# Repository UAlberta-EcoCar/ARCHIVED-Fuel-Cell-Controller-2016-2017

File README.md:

# Fuel-Cell-Controller
Custom controller for a 28 cell Ballard Fuel Cell

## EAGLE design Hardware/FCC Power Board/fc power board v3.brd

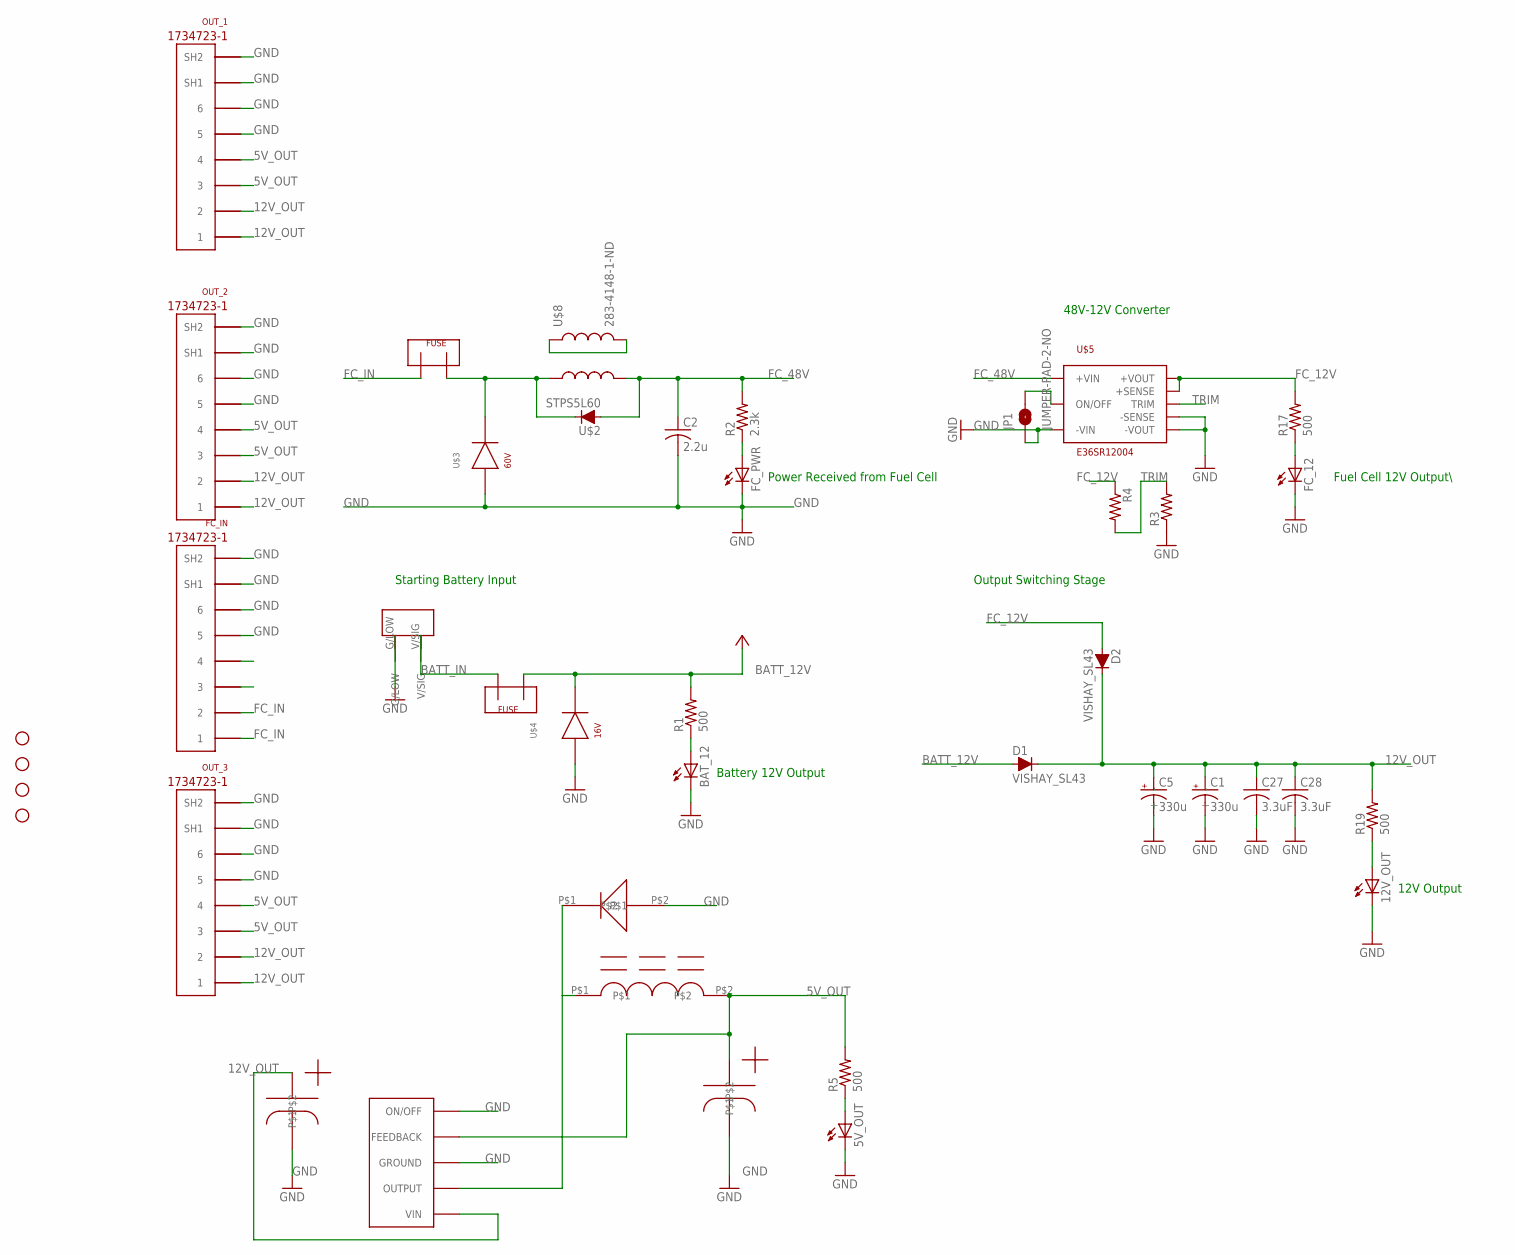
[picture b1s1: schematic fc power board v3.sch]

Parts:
5V_OUT, 12V_OUT: LED1206; LED-1206
BATTERY_FUSE: FUSEMINI-BLADE; MINI-BLADE-FUSE
BAT_12: LED1206; LED-1206
C1, C5: 330u; 399-6608-ND
C2: 2.2u; C0805
C27, C28: 3.3uF; C0805
D1, D2: VISHAY_SL43; DO-214AB_SMC
FC_12: LED1206; LED-1206
FC_IN: 5555140-6; 1734723-1_RJ11
FC_PWR: LED1206; LED-1206
JP1: JUMPER-PAD-2-NO; PAD-JUMPER-2-NO_NO_SILK
OUT_1, OUT_2, OUT_3: 5555140-6; 1734723-1_RJ11
R1, R5, R17: 500; R0805
R2: 2.3k; R0805
R3, R4: R-US_R0805; R0805
R19: 500; M0805
STANDOFF1, STANDOFF2, STANDOFF3, STANDOFF4: STAND-OFF
U$1: MBR360GOS
U$2: STPS5L60; STM_SMC
U$3: SMBJ60CA; .277X.089
U$4: SMAJ16CA; .25X.07
U$5: E36SR12004; 2.30X0.90X0.34
U$7: FUSEMINI-BLADE; MINI-BLADE-FUSE
U$8: 283-4148-1-ND
U$9: 2_PIN_TECONNECTOR; 2_PIN_CONNECT
U$13: LM2576; D2PAK-5
U$14: CAPESK107M025AC3AA; ESK107M025AC3AA
U$15: CAPESK108M025AH4EA; ESK108M025AH4EA
U$16: M1418-ND

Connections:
5V_OUT: OUT_1.3, OUT_1.4, OUT_2.3, OUT_2.4, OUT_3.3, OUT_3.4, R5.2, U$13.4 (FEEDBACK), U$15.P$1, U$16.P$2
12V_OUT: C1.PLUS (+), C5.PLUS (+), C27.1, C28.1, D1.C, D2.C, OUT_1.1, OUT_1.2, OUT_2.1, OUT_2.2, OUT_3.1, OUT_3.2, R19.2, U$13.1 (VIN), U$14.P$1
BATT_12V: BATTERY_FUSE.OUT, D1.A, R1.2, U$4.CATHODE
BATT_IN: BATTERY_FUSE.IN, U$9.V/SIG
FC_12V: D2.A, R4.1, R17.2, U$5.P$7 (+SENSE), U$5.P$8 (+VOUT)
FC_48V: C2.1, R2.2, U$2.A, U$5.P$1 (+VIN), U$8.P$3 (2)
FC_FUSED: U$2.C, U$3.CATHODE, U$7.IN, U$8.P$1 (1)
FC_IN: FC_IN.1, FC_IN.2, U$7.OUT
GND: 5V_OUT.C, 12V_OUT.C, BAT_12.C, C1.MINUS (-), C2.2, C5.MINUS (-), C27.2, C28.2, FC_12.C, FC_IN.5, FC_IN.6, FC_IN.SH1, FC_IN.SH2, FC_PWR.C, JP1.1, OUT_1.5, OUT_1.6, OUT_1.SH1, OUT_1.SH2, OUT_2.5, OUT_2.6, OUT_2.SH1, OUT_2.SH2, OUT_3.5, OUT_3.6, OUT_3.SH1, OUT_3.SH2, R3.1, U$1.P$2, U$3.ANODE, U$4.ANODE, U$5.P$3 (-VIN), U$5.P$4 (-VOUT), U$5.P$5 (-SENSE), U$9.G/LOW, U$13.3 (GROUND), U$13.5 (ON/OFF), U$13.GROUND, U$14.P$2, U$15.P$2
unnamed: JP1.2, U$5.P$2 (ON/OFF)
unnamed: BAT_12.A, R1.1
unnamed: FC_PWR.A, R2.1
unnamed: U$8.P$2 (3), U$8.P$4 (4)
unnamed: 5V_OUT.A, R5.1
unnamed: U$1.P$1, U$13.2 (OUTPUT), U$16.P$1
unnamed: FC_12.A, R17.1
unnamed: 12V_OUT.A, R19.1
TRIM: R3.2, R4.2, U$5.P$6 (TRIM)

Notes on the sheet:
Output Switching Stage
Starting Battery Input
48V-12V Converter
Power Received from Fuel Cell
Battery 12V Output
Fuel Cell 12V Output\
12V Output

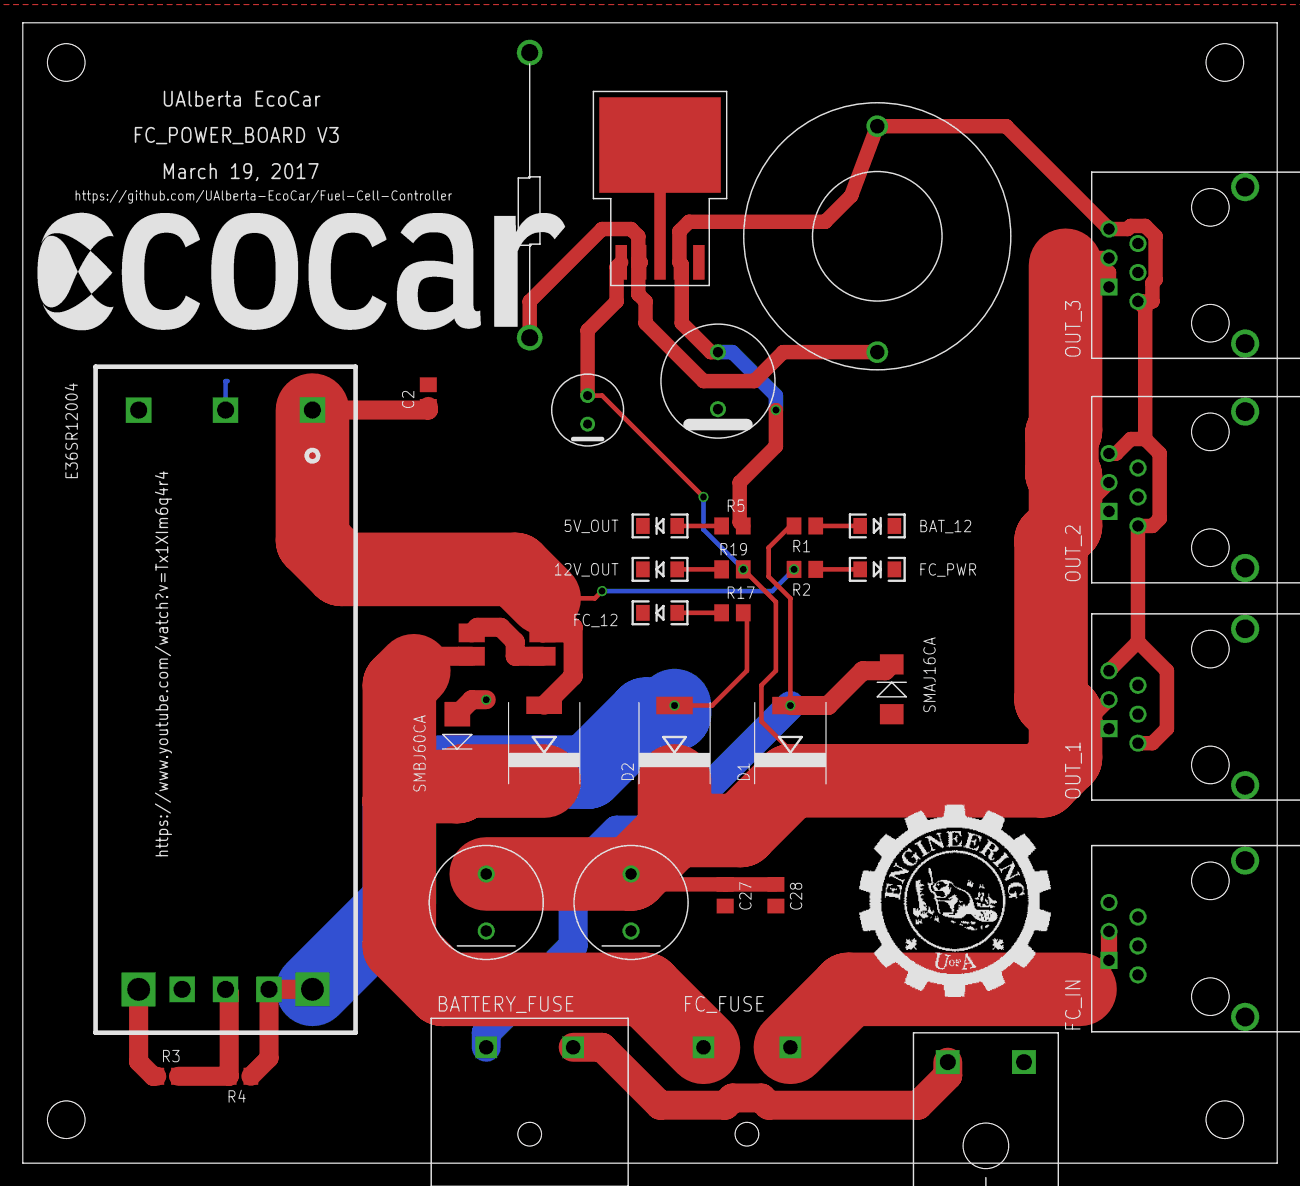
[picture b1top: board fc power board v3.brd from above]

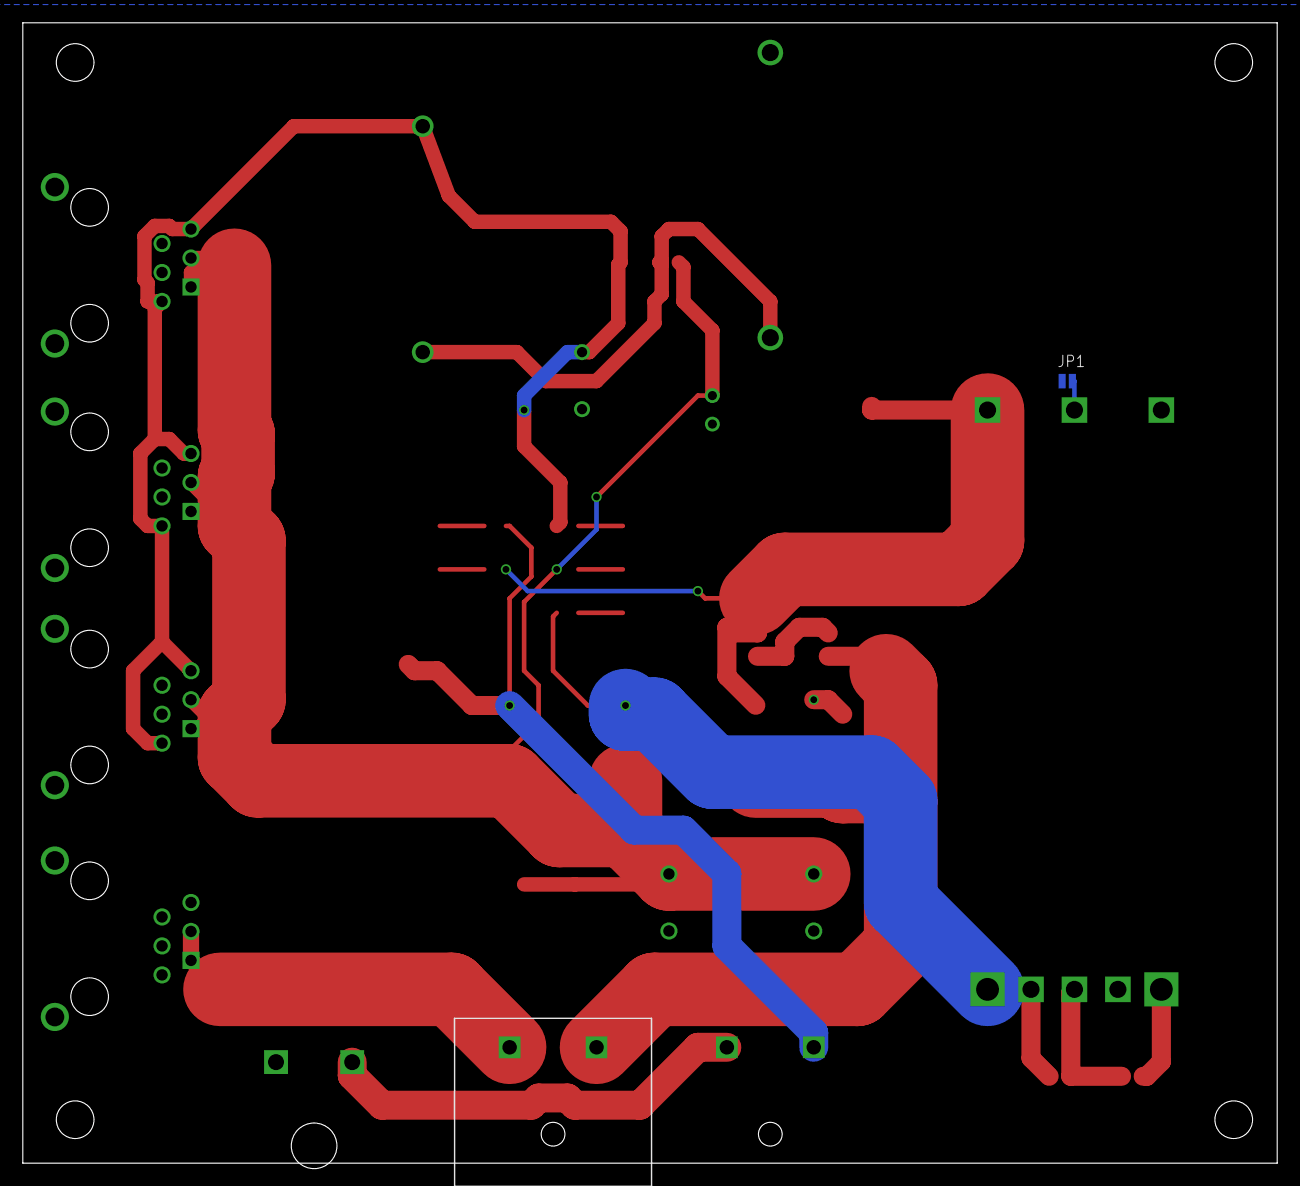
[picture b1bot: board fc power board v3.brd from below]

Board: 2 copper layers, 110.0 x 100.0 mm, 42 parts (2 on the bottom side), 18 nets.

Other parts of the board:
U$6: ECOCAR_LOGO_2018

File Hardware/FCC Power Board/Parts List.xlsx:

Capacitors
399-6608-ND |  | 2
ESK108M025AH4EA |  | 1
ESK107M025AC3AA |  | 1
3.3 uF |  | 2
Inductors
M1418-ND |  | 1
283-4148-1-ND |  | 1
Fuse Holder
F064-ND |  | 2
TVS Diode
SMAJ16CA |  | 1
SMBJ60CA |  | 1
Blocking Diodes
STPS5L60 |  | 3
MBR360GOS |  | 1
Block Power Converter
E36SR12004 |  | 1
12 to 5 regulator
LM2576D2TR4-5GOSCT-ND |  | 1
Resistors
500 |  | 3
2300 |  | 1

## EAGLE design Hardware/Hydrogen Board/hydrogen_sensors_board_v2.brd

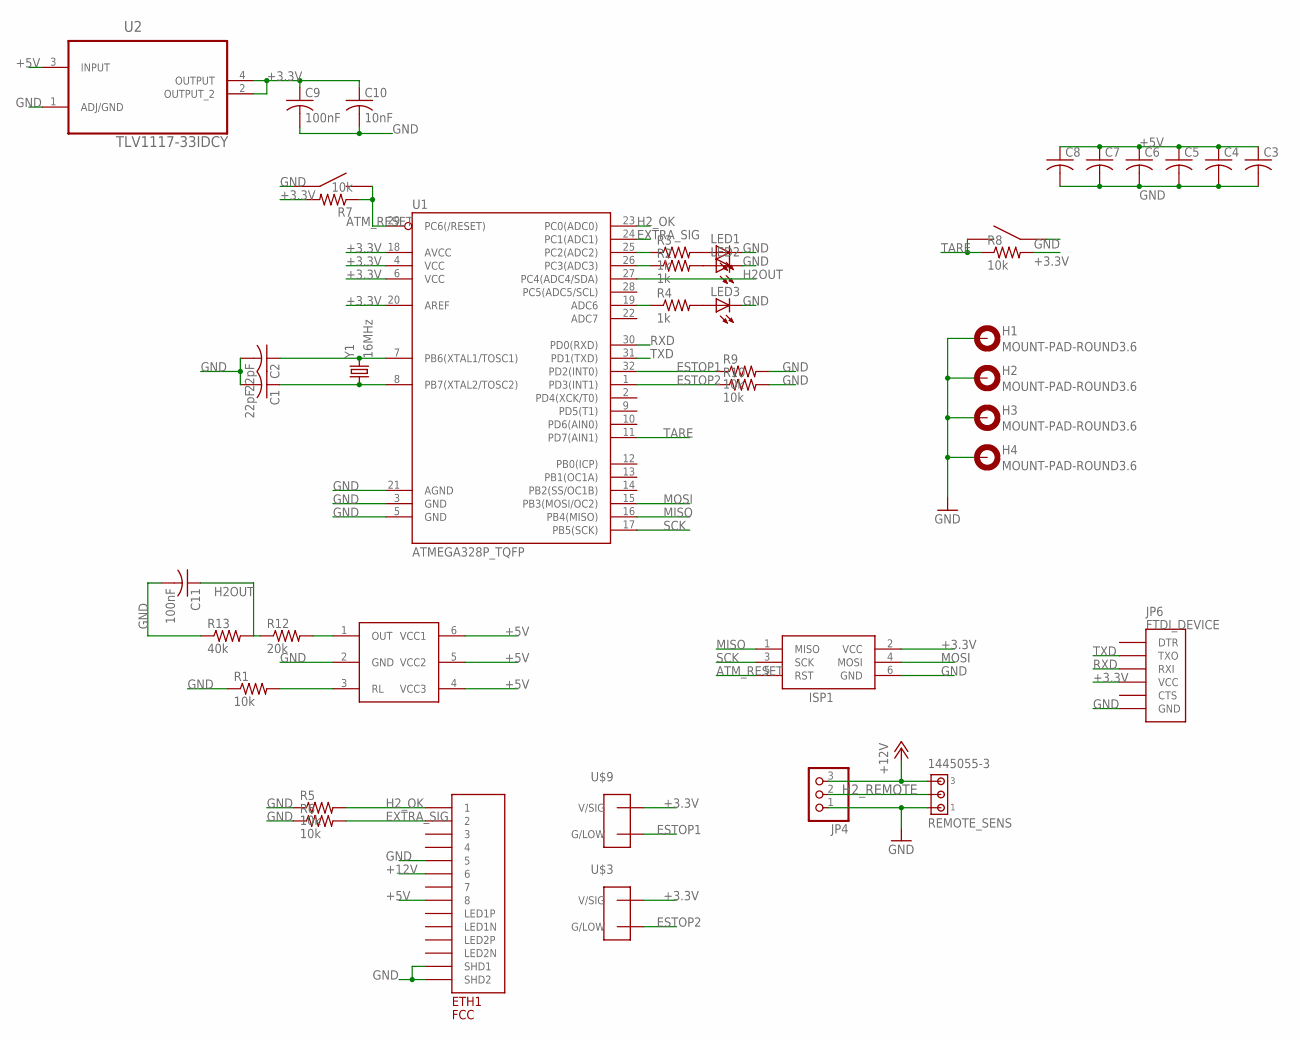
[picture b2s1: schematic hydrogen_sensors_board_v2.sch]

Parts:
C1, C2: 22pF; C0603K
C3, C4, C5, C6, C7, C8: C-USC0603; C0603
C9, C11: 100nF; C0603
C10: 10nF; C0603
ETH1: FCC; A122645-ND
H1, H2, H3, H4: MOUNT-PAD-ROUND3.6; 3,6-PAD
ISP1: AVRISP-BOX
JP4: PINHD-1X3; 1X03
JP6: FTDI_DEVICE; FTDI_DEVICE_SIDE
LED1, LED2, LED3: LEDCHIPLED_0805; CHIPLED_0805
R1, R5, R6, R7, R8, R9, R10: 10k; 0603-RES
R2, R3, R4: 1k; 0603-RES
R12: 20k; 0603-RES
R13: 40k; 0603-RES
REMOTE_SENS: 1445055-3
U1: ATMEGA328P_TQFP; TQFP32-08
U2: TLV1117-33IDCY; SOT230P700X180-4N
U$1: MQ-8MQ-8; MQ-8
U$2, U$10: EG4621CT-ND
U$3, U$9: TE770966; 2X1-MATE-N-LOCK
Y1: 16MHz; HC49US

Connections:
+3.3V: C9.1, C10.1, ISP1.2 (VCC), JP6.P$4 (VCC), R7.2, R8.2, U1.4 (VCC), U1.6 (VCC), U1.18 (AVCC), U1.20 (AREF), U2.2 (OUTPUT_2), U2.4 (OUTPUT), U$3.CIRCUIT1 (V/SIG), U$9.CIRCUIT1 (V/SIG)
+5V: C3.1, C4.1, C5.1, C6.1, C7.1, C8.1, ETH1.P$8 (8), U2.3 (INPUT), U$1.4 (VCC3), U$1.5 (VCC2), U$1.6 (VCC1)
+12V: ETH1.P$6 (6), JP4.3, REMOTE_SENS.3
ATM_RESET: ISP1.5 (RST), R7.1, U1.29 (PC6(/RESET)), U$10.P$3, U$10.P$4
ESTOP1: R9.1, U1.32 (PD2(INT0)), U$9.CIRCUIT2 (G/LOW)
ESTOP2: R10.1, U1.1 (PD3(INT1)), U$3.CIRCUIT2 (G/LOW)
EXTRA_SIG: ETH1.P$2 (2), R6.2, U1.24 (PC1(ADC1))
GND: C1.2, C2.2, C3.2, C4.2, C5.2, C6.2, C7.2, C8.2, C9.2, C10.2, C11.2, ETH1.P$5 (5), ETH1.P$13 (SHD1), ETH1.P$14 (SHD2), H1.B3,6, H2.B3,6, H3.B3,6, H4.B3,6, ISP1.6 (GND), JP4.1, JP6.P$6 (GND), LED1.C, LED2.C, LED3.C, R1.1, R5.1, R6.1, R9.2, R10.2, R13.1, REMOTE_SENS.1, U1.3 (GND), U1.5 (GND), U1.21 (AGND), U2.1 (ADJ/GND), U$1.2 (GND), U$2.P$1, U$2.P$2, U$10.P$1, U$10.P$2
H2OUT: C11.1, R12.1, R13.2, U1.27 (PC4(ADC4/SDA))
H2_OK: ETH1.P$1 (1), R5.2, U1.23 (PC0(ADC0))
H2_REMOTE: JP4.2, REMOTE_SENS.2
MISO: ISP1.1 (MISO), U1.16 (PB4(MISO))
MOSI: ISP1.4 (MOSI), U1.15 (PB3(MOSI/OC2))
unnamed: C2.1, U1.7 (PB6(XTAL1/TOSC1)), Y1.2
unnamed: R1.2, U$1.3 (RL)
unnamed: C1.1, U1.8 (PB7(XTAL2/TOSC2)), Y1.1
unnamed: R3.1, U1.25 (PC2(ADC2))
unnamed: R2.1, U1.26 (PC3(ADC3))
unnamed: R4.1, U1.19 (ADC6)
unnamed: LED1.A, R3.2
unnamed: LED2.A, R2.2
unnamed: LED3.A, R4.2
unnamed: R12.2, U$1.1 (OUT)
RXD: JP6.P$3 (RXI), U1.30 (PD0(RXD))
SCK: ISP1.3 (SCK), U1.17 (PB5(SCK))
TARE: R8.1, U1.11 (PD7(AIN1)), U$2.P$3, U$2.P$4
TXD: JP6.P$2 (TXO), U1.31 (PD1(TXD))

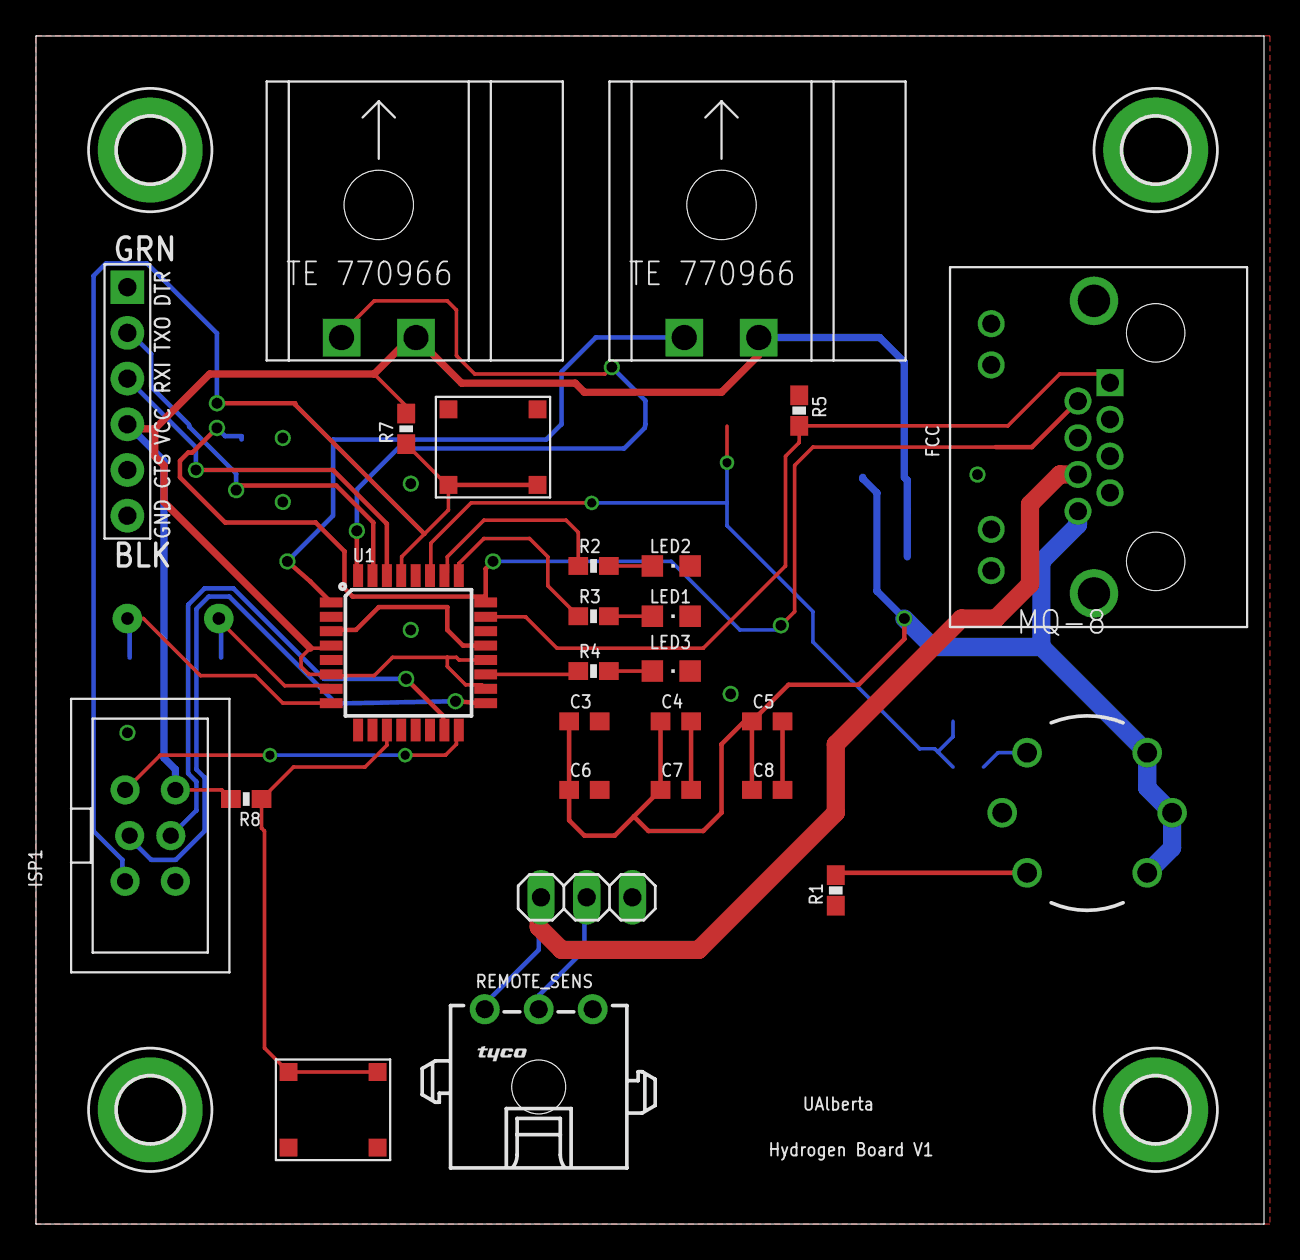
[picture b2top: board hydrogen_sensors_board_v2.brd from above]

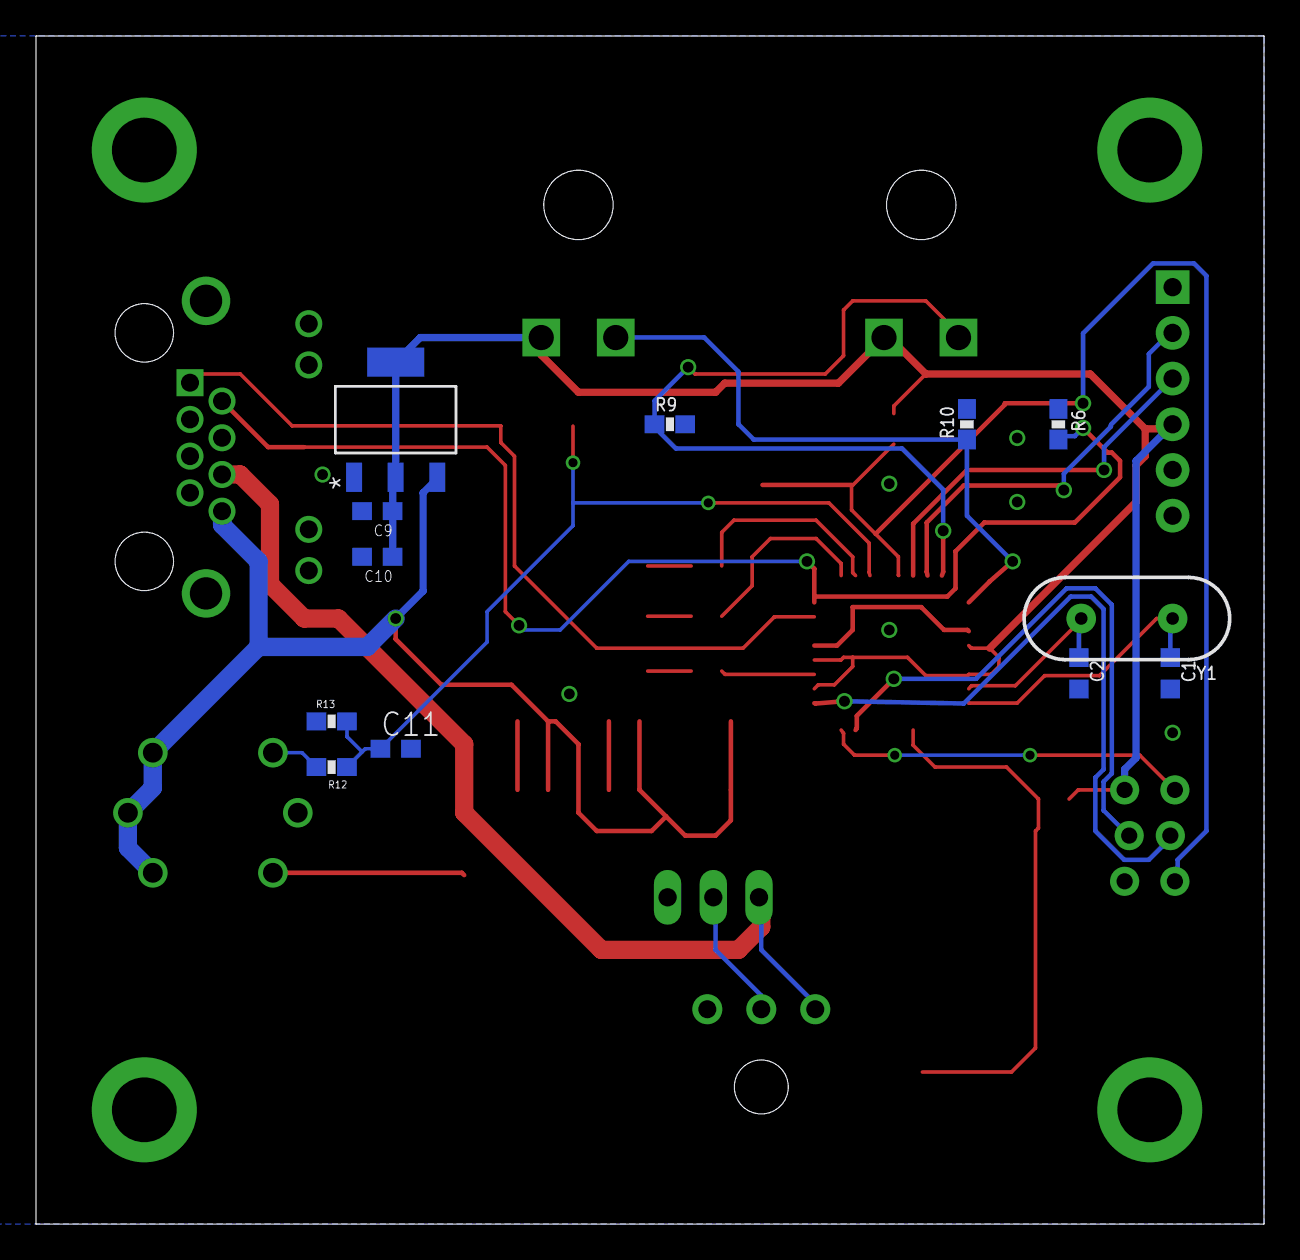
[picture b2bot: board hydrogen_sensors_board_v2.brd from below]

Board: 2 copper layers, 68.2 x 66.0 mm, 43 parts (12 on the bottom side), 27 nets.

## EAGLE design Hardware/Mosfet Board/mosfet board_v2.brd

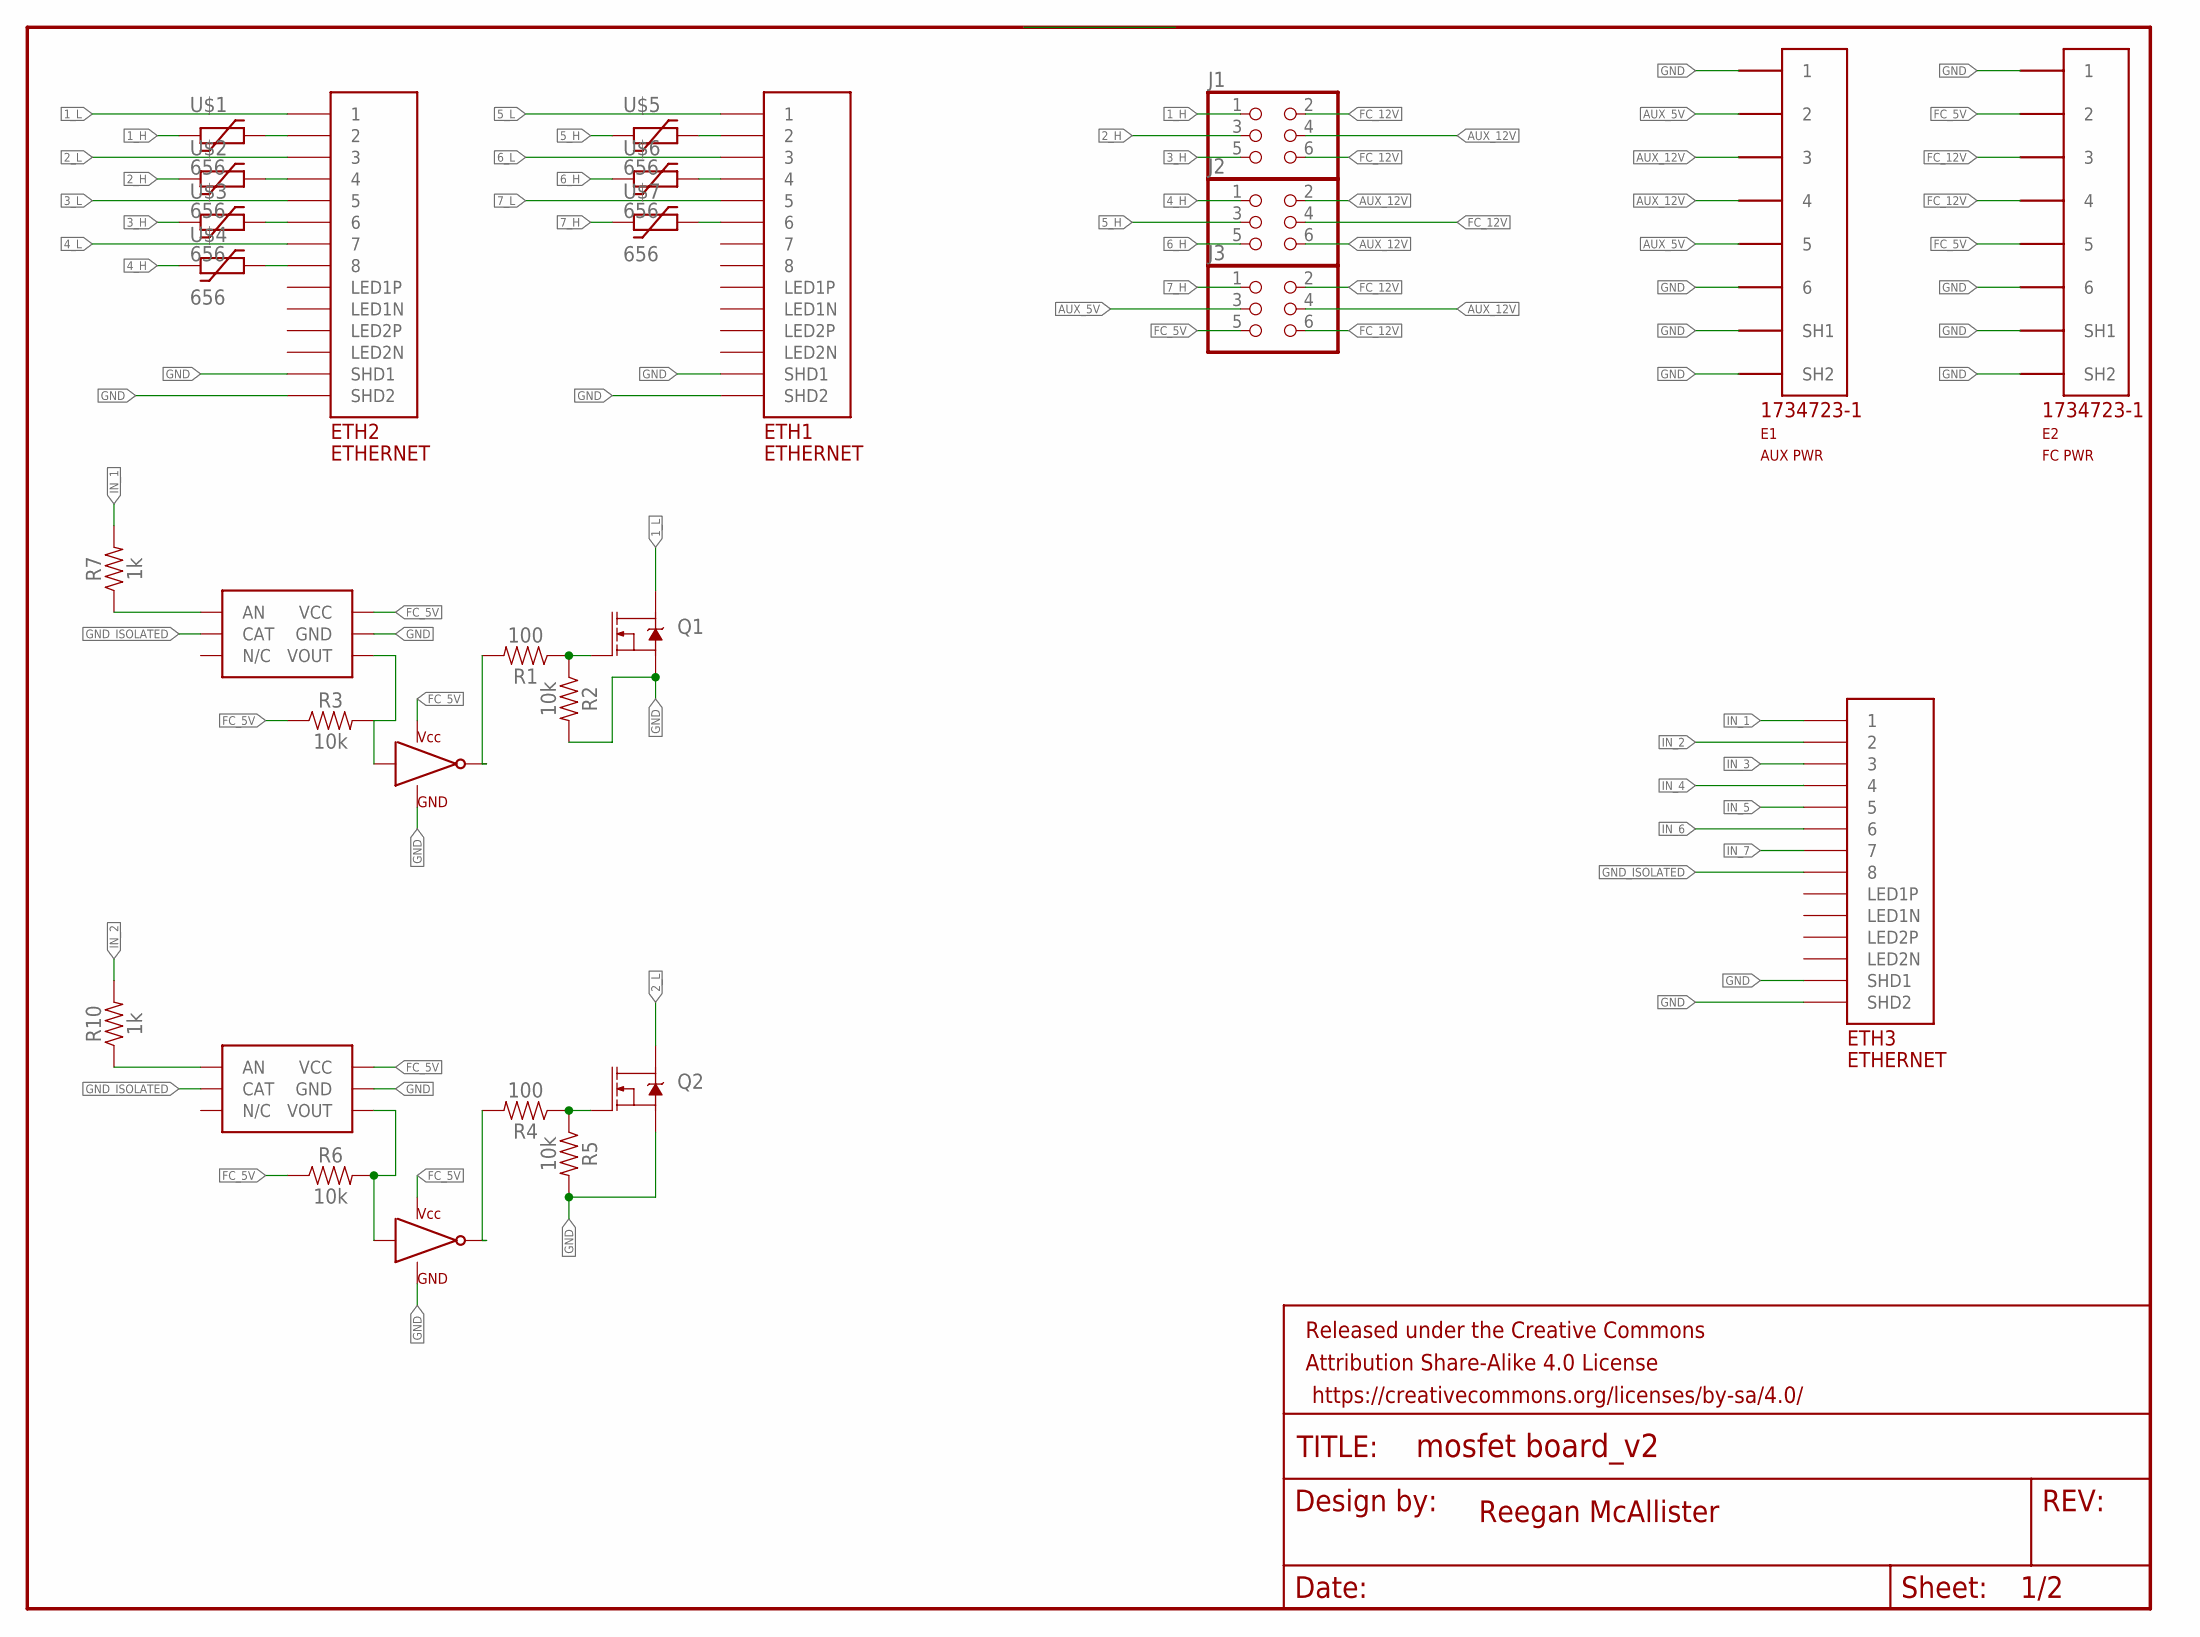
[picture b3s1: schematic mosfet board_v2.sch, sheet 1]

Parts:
E1: AUX PWR; 1734723-1_RJ11
E2: FC PWR; 1734723-1_RJ11
ETH1, ETH2, ETH3: ETHERNET; A122645-ND
FRAME1: FRAME-LETTERNO_PACKAGE; DUMMY
J1, J2, J3: PINHD-2X3; 2X03
Q1, Q2: MOSFET-NCH-AO3404A; SOT23-3
R1, R4: 100; 0805
R2, R3, R5, R6: 10k; 0805
R7, R10: 1k; 0805
U$1, U$2, U$3, U$4, U$5, U$6, U$7: 656
U$8, U$10: H11L1M
U$9, U$11: SN74LVC1G04-Q1; SOT-23-5

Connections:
1_H: J1.1, U$1.P$1 (1)
1_L: ETH2.P$1 (1), Q1.3 (D)
2_H: J1.3, U$2.P$1 (1)
2_L: ETH2.P$3 (3), Q2.3 (D)
3_H: J1.5, U$3.P$1 (1)
3_L: ETH2.P$5 (5); also elsewhere on the board
4_H: J2.1, U$4.P$1 (1)
4_L: ETH2.P$7 (7); also elsewhere on the board
5_H: J2.3, U$5.P$1 (1)
5_L: ETH1.P$1 (1); also elsewhere on the board
6_H: J2.5, U$6.P$1 (1)
6_L: ETH1.P$3 (3); also elsewhere on the board
7_H: J3.1, U$7.P$1 (1)
7_L: ETH1.P$5 (5); also elsewhere on the board
AUX_5V: E1.2, E1.5, J3.3
AUX_12V: E1.3, E1.4, J1.4, J2.2, J2.6, J3.4
FC_5V: E2.2, E2.5, J3.5, R3.1, R6.1, U$8.P$6 (VCC), U$9.P$5 (VCC), U$10.P$6 (VCC), U$11.P$5 (VCC); also elsewhere on the board
FC_12V: E2.3, E2.4, J1.2, J1.6, J2.4, J3.2, J3.6
GND: E1.1, E1.6, E1.SH1, E1.SH2, E2.1, E2.6, E2.SH1, E2.SH2, ETH1.P$13 (SHD1), ETH1.P$14 (SHD2), ETH2.P$13 (SHD1), ETH2.P$14 (SHD2), ETH3.P$13 (SHD1), ETH3.P$14 (SHD2), Q1.2 (S), Q2.2 (S), R2.2, R5.2, U$8.P$5 (GND), U$9.P$1 (GND), U$9.P$3 (GND), U$10.P$5 (GND), U$11.P$1 (GND), U$11.P$3 (GND); also elsewhere on the board
GND_ISOLATED: ETH3.P$8 (8), U$8.P$2 (CAT), U$10.P$2 (CAT); also elsewhere on the board
IN_1: ETH3.P$1 (1), R7.2
IN_2: ETH3.P$2 (2), R10.2
IN_3: ETH3.P$3 (3); also elsewhere on the board
IN_4: ETH3.P$4 (4); also elsewhere on the board
IN_5: ETH3.P$5 (5); also elsewhere on the board
IN_6: ETH3.P$6 (6); also elsewhere on the board
IN_7: ETH3.P$7 (7); also elsewhere on the board
unnamed: ETH2.P$2 (2), U$1.P$2 (2)
unnamed: ETH2.P$4 (4), U$2.P$2 (2)
unnamed: ETH2.P$6 (6), U$3.P$2 (2)
unnamed: ETH2.P$8 (8), U$4.P$2 (2)
unnamed: ETH1.P$2 (2), U$5.P$2 (2)
unnamed: Q1.1 (G), R1.1, R2.1
unnamed: R3.2, U$8.P$4 (VOUT), U$9.P$2 (IN)
unnamed: R1.2, U$9.P$4 (OUT)
unnamed: ETH1.P$6 (6), U$7.P$2 (2)
unnamed: ETH1.P$4 (4), U$6.P$2 (2)
unnamed: Q2.1 (G), R4.1, R5.1
unnamed: R6.2, U$10.P$4 (VOUT), U$11.P$2 (IN)
unnamed: R4.2, U$11.P$4 (OUT)
unnamed: R10.1, U$10.P$1 (AN)
unnamed: R7.1, U$8.P$1 (AN)

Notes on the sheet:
Reegan McAllister

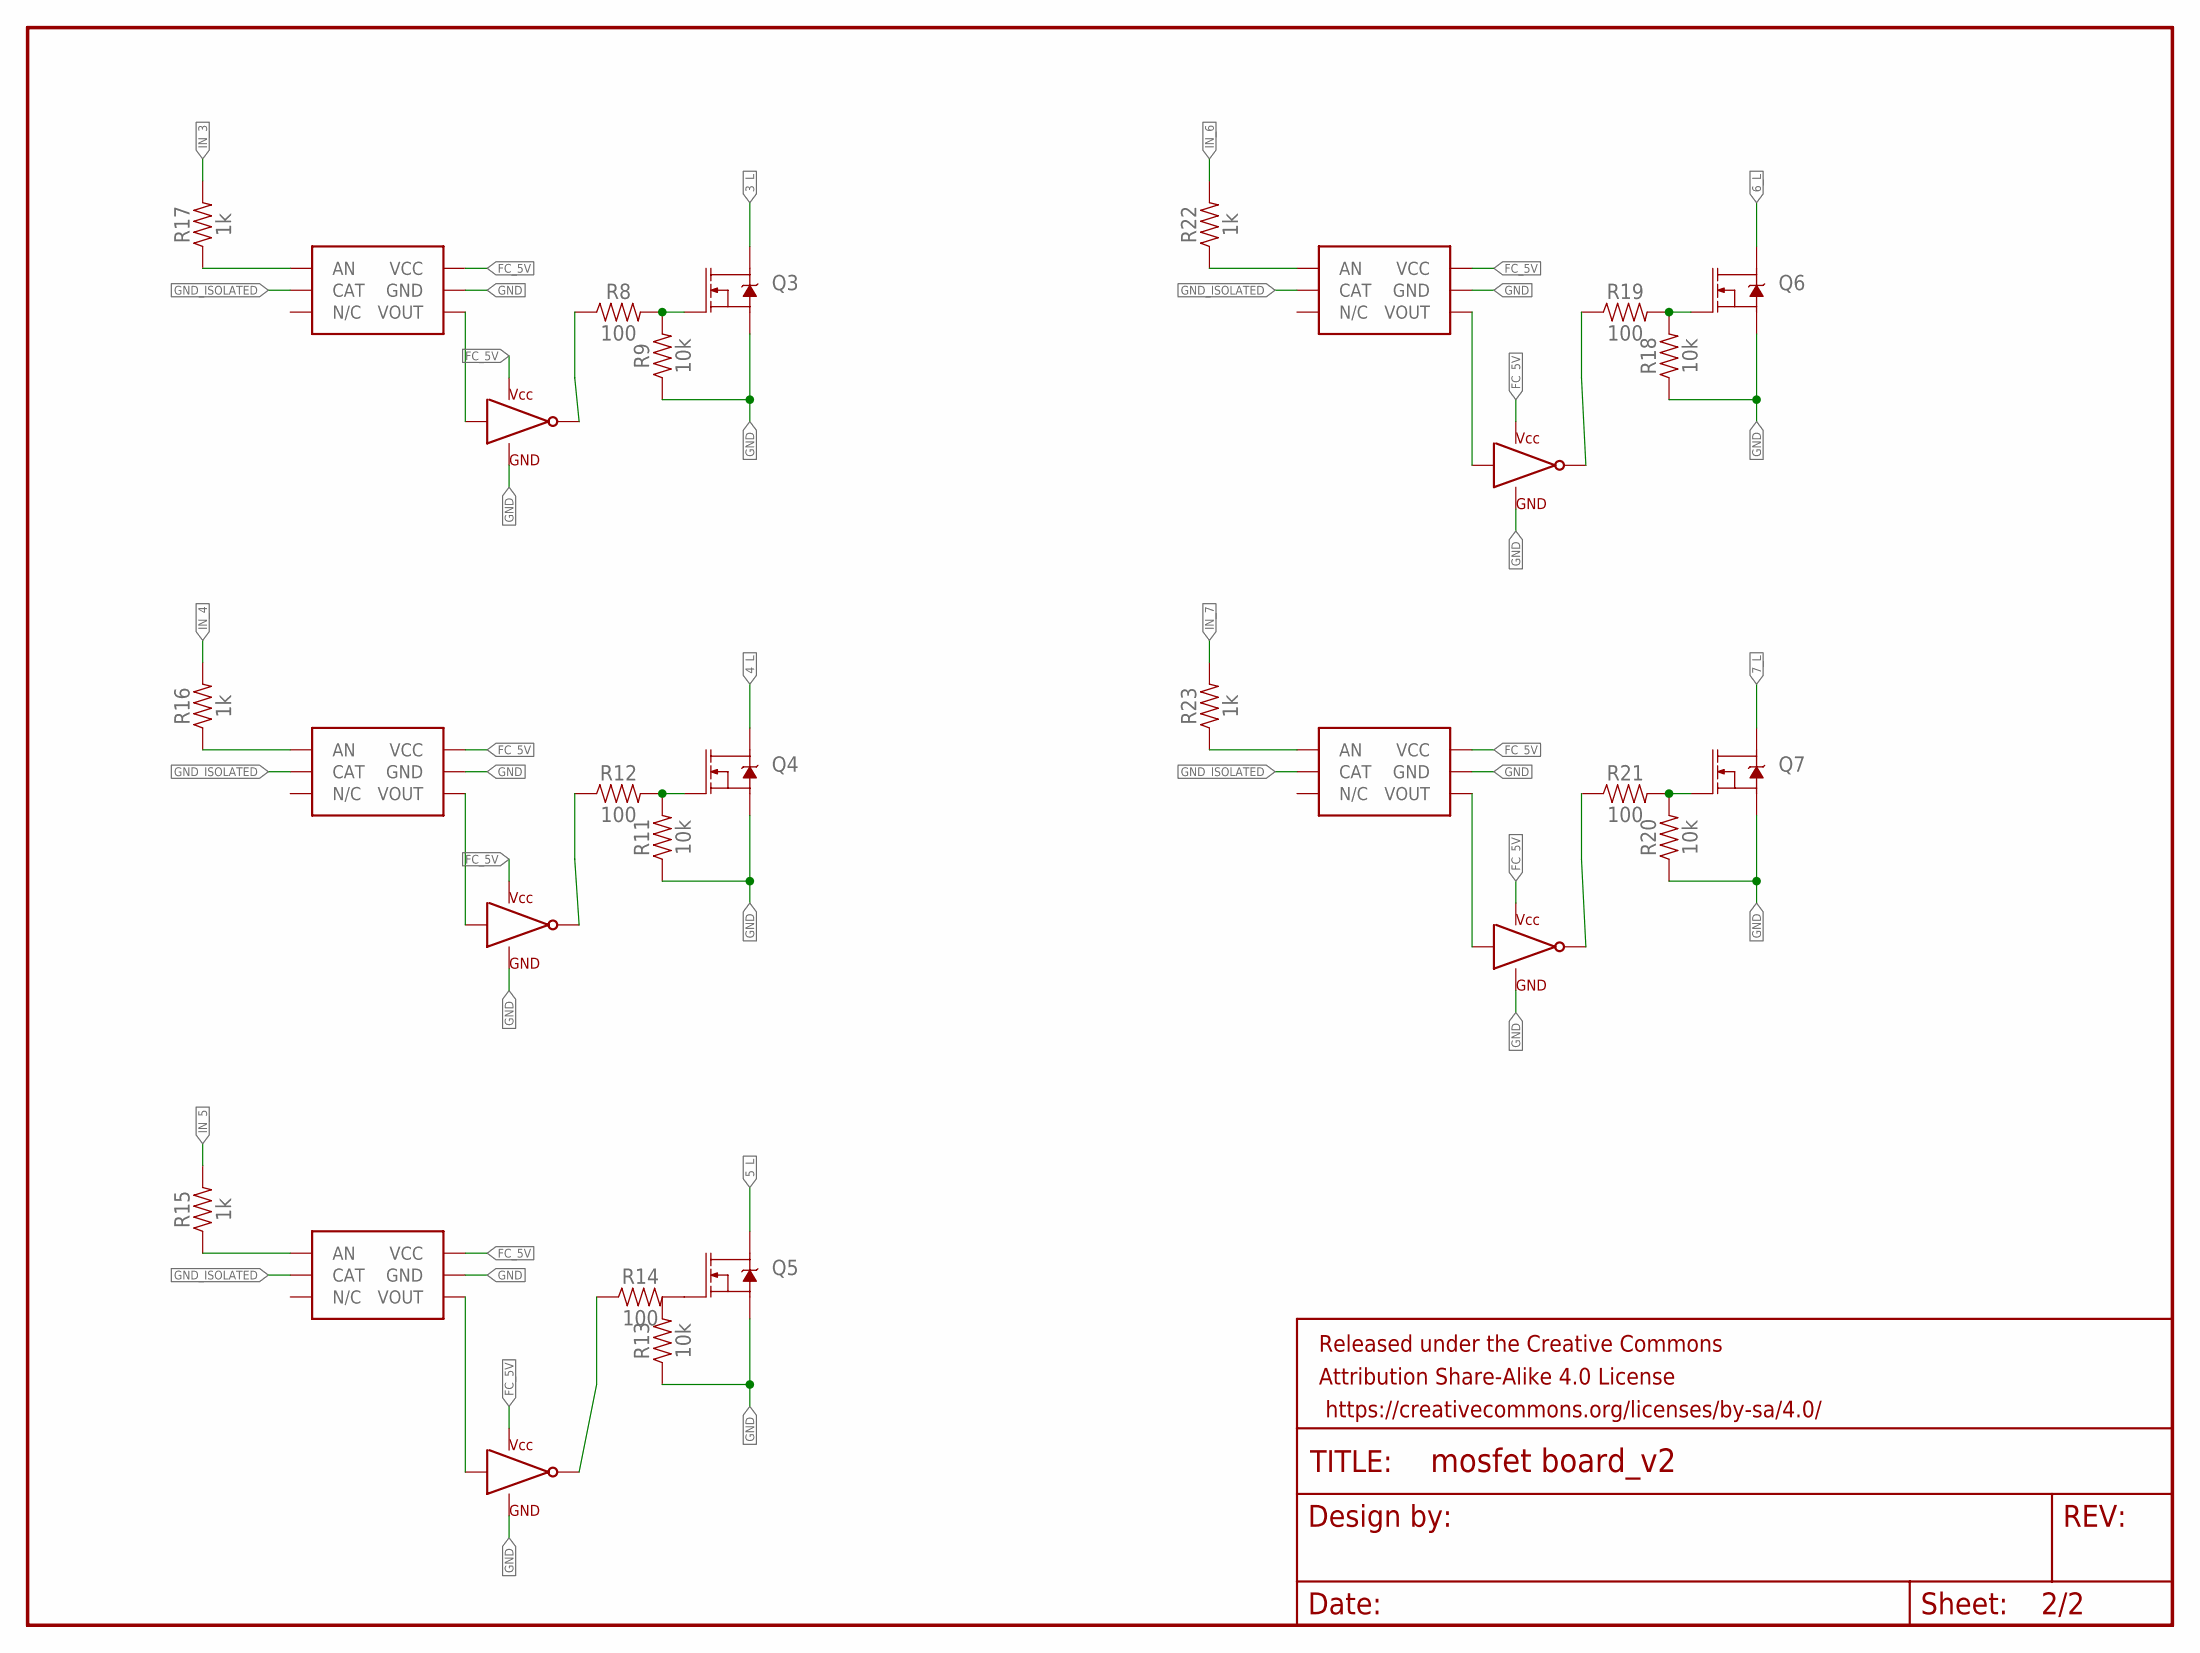
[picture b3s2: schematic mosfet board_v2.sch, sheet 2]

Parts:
FRAME2: FRAME-LETTERNO_PACKAGE; DUMMY
Q3, Q4, Q5, Q6, Q7: MOSFET-NCH-AO3404A; SOT23-3
R8, R12, R14, R19, R21: 100; 0805
R9, R11, R13, R18, R20: 10k; 0805
R15, R16, R17, R22, R23: 1k; 0805
U$12, U$14, U$16, U$18, U$20: H11L1M
U$13, U$15, U$17, U$19, U$21: SN74LVC1G04-Q1; SOT-23-5

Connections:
3_L: Q3.3 (D); also elsewhere on the board
4_L: Q4.3 (D); also elsewhere on the board
5_L: Q5.3 (D); also elsewhere on the board
6_L: Q6.3 (D); also elsewhere on the board
7_L: Q7.3 (D); also elsewhere on the board
FC_5V: U$12.P$6 (VCC), U$13.P$5 (VCC), U$14.P$6 (VCC), U$15.P$5 (VCC), U$16.P$6 (VCC), U$17.P$5 (VCC), U$18.P$6 (VCC), U$19.P$5 (VCC), U$20.P$6 (VCC), U$21.P$5 (VCC); also elsewhere on the board
GND: Q3.2 (S), Q4.2 (S), Q5.2 (S), Q6.2 (S), Q7.2 (S), R9.1, R11.1, R13.1, R18.1, R20.1, U$12.P$5 (GND), U$13.P$1 (GND), U$13.P$3 (GND), U$14.P$5 (GND), U$15.P$1 (GND), U$15.P$3 (GND), U$16.P$5 (GND), U$17.P$1 (GND), U$17.P$3 (GND), U$18.P$5 (GND), U$19.P$1 (GND), U$19.P$3 (GND), U$20.P$5 (GND), U$21.P$1 (GND), U$21.P$3 (GND); also elsewhere on the board
GND_ISOLATED: U$12.P$2 (CAT), U$14.P$2 (CAT), U$16.P$2 (CAT), U$18.P$2 (CAT), U$20.P$2 (CAT); also elsewhere on the board
IN_3: R17.2; also elsewhere on the board
IN_4: R16.2; also elsewhere on the board
IN_5: R15.2; also elsewhere on the board
IN_6: R22.2; also elsewhere on the board
IN_7: R23.2; also elsewhere on the board
unnamed: Q3.1 (G), R8.2, R9.2
unnamed: Q4.1 (G), R11.2, R12.2
unnamed: Q5.1 (G), R14.2
unnamed: Q6.1 (G), R18.2, R19.2
unnamed: Q7.1 (G), R20.2, R21.2
unnamed: R17.1, U$12.P$1 (AN)
unnamed: R16.1, U$14.P$1 (AN)
unnamed: R15.1, U$16.P$1 (AN)
unnamed: R22.1, U$18.P$1 (AN)
unnamed: R23.1, U$20.P$1 (AN)
unnamed: U$12.P$4 (VOUT), U$13.P$2 (IN)
unnamed: R8.1, U$13.P$4 (OUT)
unnamed: U$16.P$4 (VOUT), U$17.P$2 (IN)
unnamed: R14.1, U$17.P$4 (OUT)
unnamed: U$14.P$4 (VOUT), U$15.P$2 (IN)
unnamed: R12.1, U$15.P$4 (OUT)
unnamed: U$20.P$4 (VOUT), U$21.P$2 (IN)
unnamed: R21.1, U$21.P$4 (OUT)
unnamed: U$18.P$4 (VOUT), U$19.P$2 (IN)
unnamed: R19.1, U$19.P$4 (OUT)

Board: 2 copper layers, 61 parts (0 on the bottom side), 62 nets, no tracks yet.

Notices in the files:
parts and their libraries:
SparkFun-Aesthetics: Licensing: Creative Commons ShareAlike 4.0 International - https://creativecommons.org/licenses/by-sa/4.0
SparkFun-Aesthetics: Released under the Creative Commons Attribution Share-Alike 4.0 License
SparkFun-Aesthetics: https://creativecommons.org/licenses/by-sa/4.0
